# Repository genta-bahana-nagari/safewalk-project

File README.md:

# Blind Stick Project - Safewalk

This project uses **two HC-SR04 ultrasonic sensors** to measure the distance of nearby objects. If **either sensor** detects an object closer than a defined threshold (50 cm by default), a **buzzer** is triggered.

## 🚀 Features

- Dual HC-SR04 sensor support
- Real-time distance measurement via Serial Monitor
- Buzzer alert when object detected within threshold distance
- Easy to customize and expand

## 🛠️ Hardware Required

- 1 × ESP8266 or NodeMCU (or any Arduino-compatible board)
- 2 × HC-SR04 ultrasonic sensors
- 1 × Buzzer (active or passive)
- Jumper wires
- Breadboard (optional)

## 🖥️ Pin Configuration

| Component       | Pin        |
|-----------------|------------|
| Sensor 1 TRIG   | D1         |
| Sensor 1 ECHO   | D2         |
| Sensor 2 TRIG   | D3         |
| Sensor 2 ECHO   | D4         |
| Buzzer          | D0         |

> ⚠️ Make sure your sensor's ECHO pins are 5V tolerant or use a voltage divider if needed.

## 📦 How to Use

1. Connect the components as described above.
2. Upload the sketch to your board using the Arduino IDE.
3. Open the **Serial Monitor** at 9600 baud.
4. Place objects near the sensors to test proximity detection.
5. When either sensor detects an object closer than the threshold, the buzzer will beep.

## 🧠 Code Overview

```cpp
#define triggerPin1 D1
#define echoPin1    D2
#define triggerPin2 D3
#define echoPin2    D4
#define buzzer      D0
#define THRESHOLD   50

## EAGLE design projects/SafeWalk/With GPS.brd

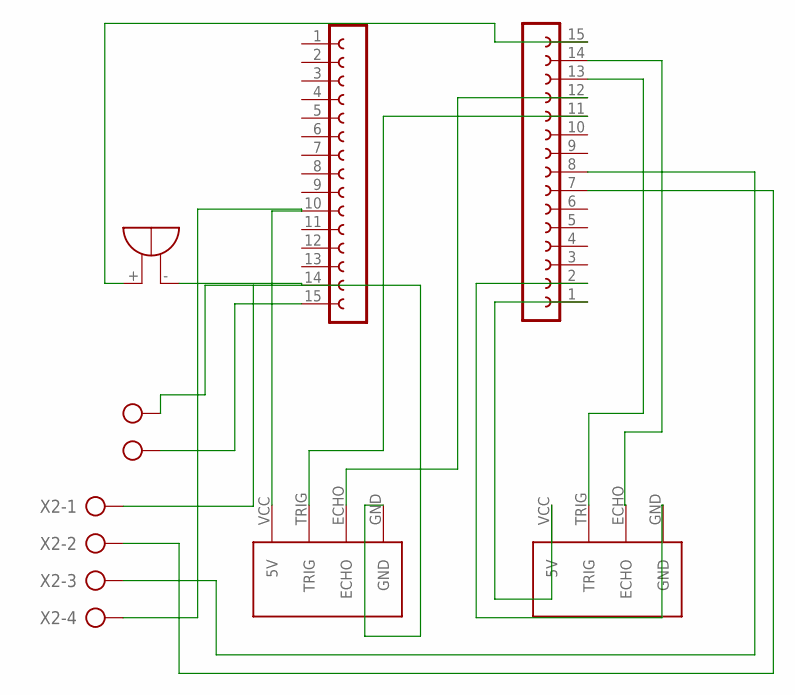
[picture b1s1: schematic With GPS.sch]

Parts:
J_ULTRASONIC_3, J_ULTRASONIC_4: HC-SR04; HC-SR04_FOOTPRINT
SG2: EB2505
SV1, SV2: FE15-1; FE15
X1: AK500/2-H
X2: AK300/4

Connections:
unnamed: J_ULTRASONIC_3.ECHO, SV1.14
unnamed: J_ULTRASONIC_3.TRIG, SV1.13
unnamed: J_ULTRASONIC_3.GND, SV1.2
unnamed: J_ULTRASONIC_3.VCC (5V), SV1.1
unnamed: SV2.15, X1.2
unnamed: SG2.+, SV1.15
unnamed: J_ULTRASONIC_4.ECHO, SV1.12
unnamed: J_ULTRASONIC_4.TRIG, SV1.11
unnamed: J_ULTRASONIC_4.VCC (5V), SV2.10, X2.4
unnamed: SV1.8, X2.3
unnamed: SV1.7, X2.2
unnamed: J_ULTRASONIC_4.GND, SG2.-, SV2.14, X1.1, X2.1

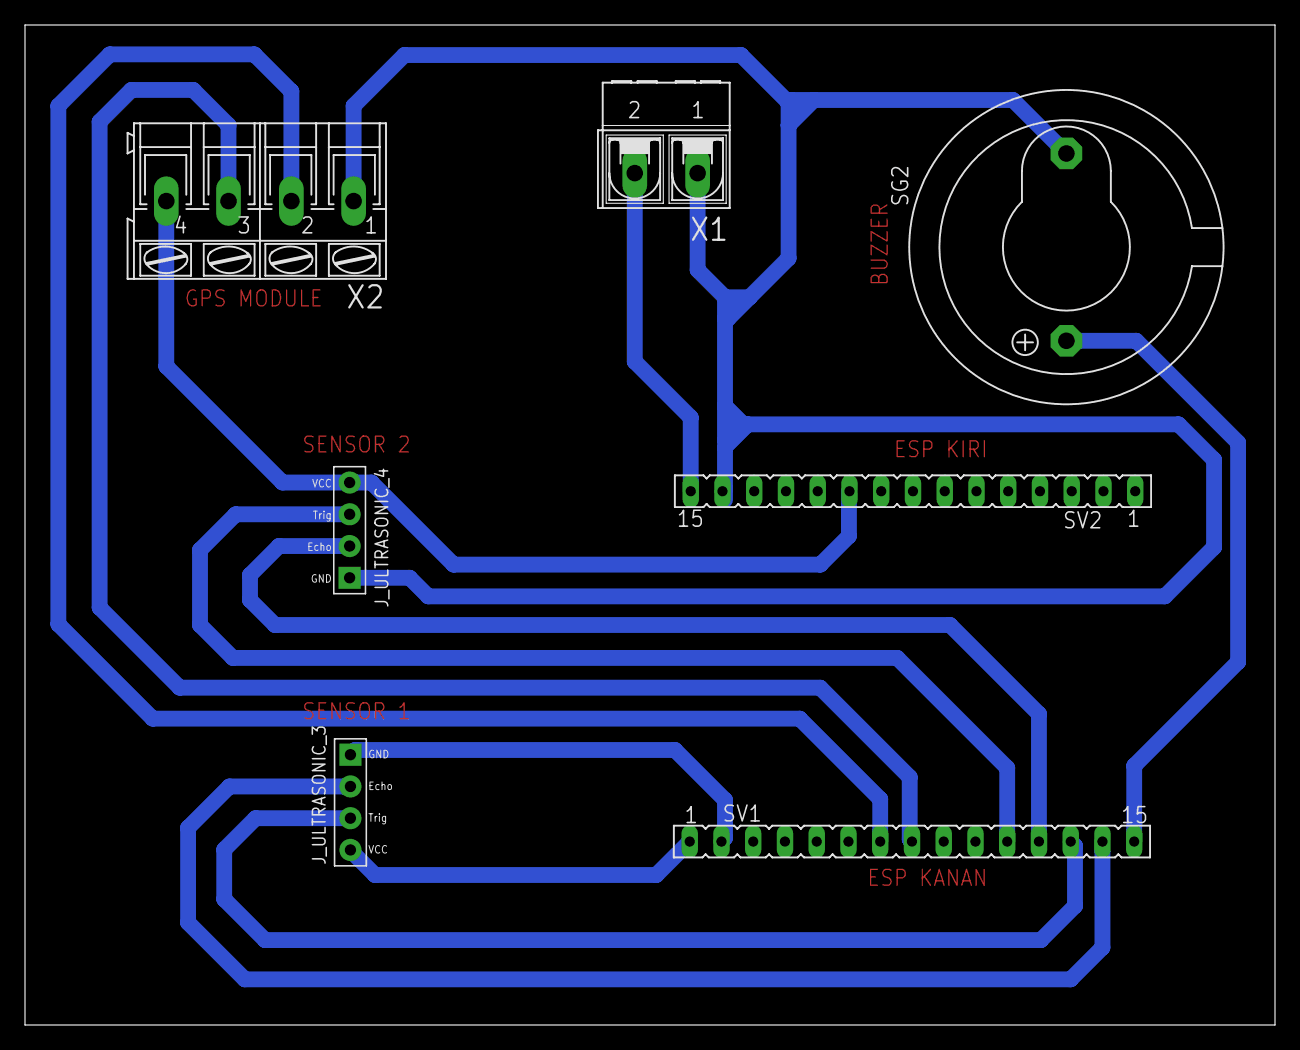
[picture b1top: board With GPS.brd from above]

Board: 2 copper layers, 100.0 x 80.0 mm, 7 parts (0 on the bottom side), 12 nets.

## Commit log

2025-04-29 schema and libraries
2025-04-30 Upload project & libraries
2025-05-02 semoga fix
2025-05-02 board 1
2025-05-04 upload malam ini
2025-05-05 GPS done laptop Adzima
